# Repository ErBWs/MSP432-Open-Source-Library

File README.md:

# MSP432-Open-Source-Library

欢迎pull request，不过请保持代码风格一致。

> 外设库放在 `/src/bsp` 文件夹内；
> 
> 代码文件命名风格：小写+下划线 `e.g. baudrate_calculate.c`；
> 
> 函数命名风格：首字母全部大写，尽量不用下划线 `e.g. GetPinLevel()`；
> 
> 函数命名下划线适用情况：同名函数但是属于不同的外设库，比如不同屏幕的显示函数，
> 
> 或者如官方库那样以函数作用来命名，名称很长且要表明是哪个库的函数（请尽量避免这种情况），
> 
> `e.g. TFT180_DisplayUint(), IPS200_DisplayUint()`，
> 
> `GPIO_SetAsInputPinWithPullDownResistor()`；
> 
> 变量名命名风格: 第一个首字母小写，后面都大写 `e.g. baudRate`；

如果代码风格不一致的pull request不一定会被退回但是会被我修改代码风格

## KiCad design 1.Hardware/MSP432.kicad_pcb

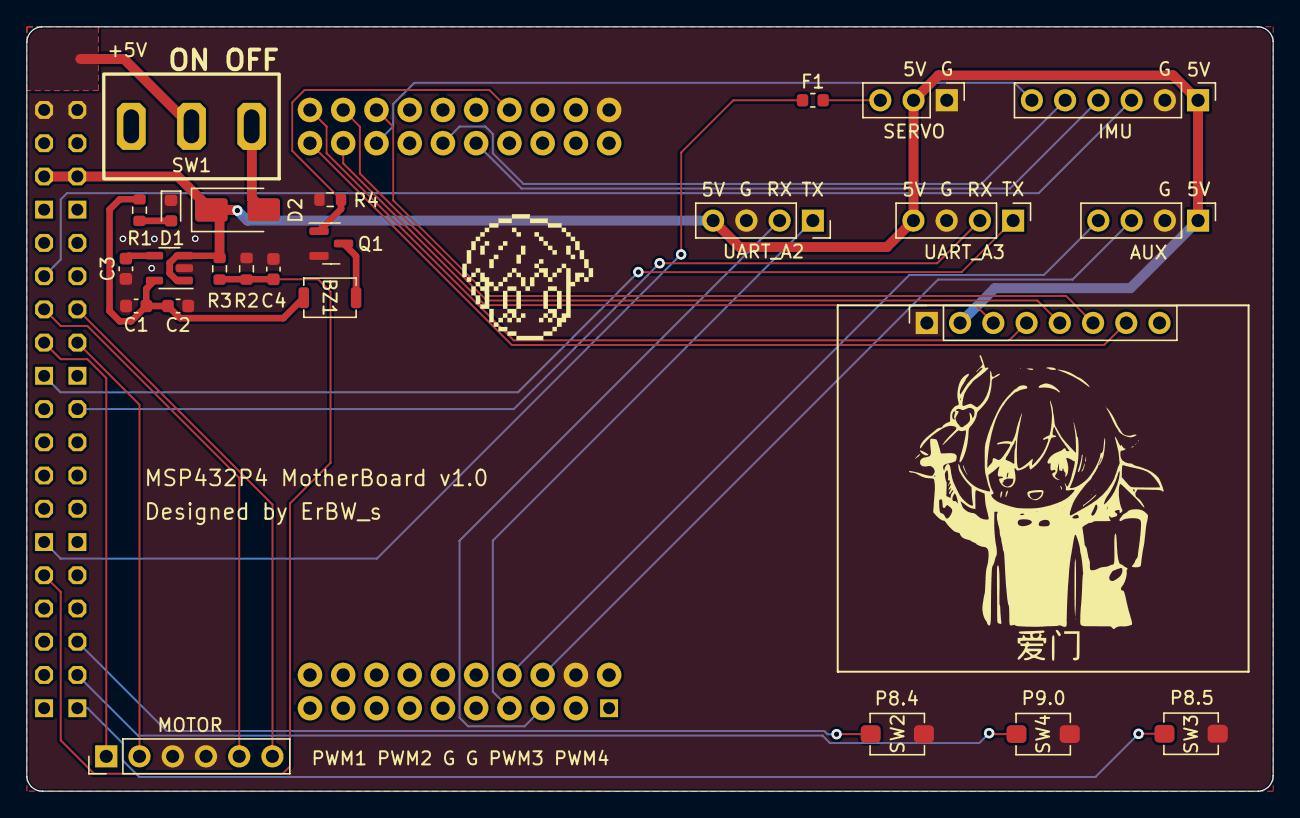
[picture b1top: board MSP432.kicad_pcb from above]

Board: 2 copper layers, 95.2 x 58.4 mm, 26 parts (1 on the bottom side), 33 nets.

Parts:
BZ1: Buzzer; DET-402-G-1
C1: 100nF; C_0603_1608Metric
C2, C4: 10uF; C_0603_1608Metric
C3: 10nF; C_0603_1608Metric
D1: LED; LED_0603_1608Metric
D2: 1N4148W; D_SMA
F1: 500mA; Fuse_0603_1608Metric
J1: SERVO; PinHeader_1x03_P2.54mm_Vertical
J2, J6: Conn_01x06; PinHeader_1x06_P2.54mm_Vertical
J3, J7: Conn_01x04; PinHeader_1x04_P2.54mm_Vertical
J4: Conn_01x08; PinSocket_1x08_P2.54mm_Vertical
J5: Conn_01x04; PinSocket_1x04_P2.54mm_Vertical
Q1: S8050; SOT-23
R1: 5K1; R_0603_1608Metric
R2: 10K; R_0603_1608Metric
R3: 1K; R_0603_1608Metric
R?: 5K1; R_0603_1608Metric
SW1: SW_SPDT; SPDT_MTS_102
SW2, SW3, SW4: 3x4; BUTTON_3x4
U1: RT9013-33GB; SOT-23-5
U2: MSP-EXP432P401R

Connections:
+3V3: BZ1.1 (-), C1.1, C2.1, R1.1, U1.5 (VOUT)
+5V: D2.1 (K), J1.2, J3.4, J4.2, J5.4, J6.1, J7.1, R2.1, U1.1 (VIN), U1.3 (EN), U2.73 (5V), U2.74 (5V)
/A2_RX: J5.2, U2.3 (P3.2/PM_UCA2RXD/PM_UCA2SOMI)
/A2_TX: J5.1, U2.4 (P3.3/PM_UCA2TXD/PM_UCA2SIMO)
/A3_RX: J3.2, U2.60 (P9.6/UCA3RXD/UCA3SOMI)
/A3_TX: J3.1, U2.61 (P9.7/UCA3TXD/UCA3SIMO)
/AUX_SCL: J7.3, U2.23 (P6.1/A14)
/AUX_SDA: J7.4, U2.24 (P4.0/A13)
/BATTERY: C4.2, R2.2, R3.1, U2.49 (P5.3/A2)
/BUZZER: Q1.1 (B), R?.1, U2.17 (P5.7/TA2.2/VREF-/VEREF-/C1.6)
/DIR1: J2.2, U2.64 (P7.4/PM_TA1.4/C0.5)
/DIR2: J2.6, U2.66 (P7.6/PM_TA1.2/C0.3)
/ENCODER_A: SW2.1, U2.46 (P8.4/A21)
/ENCODER_B: SW3.1, U2.42 (P8.5/A20)
/IMU_CS: J6.6, U2.33 (P5.1/A4)
/IMU_SDI: J6.4, U2.36 (P6.6/TA2.3/UCB3SIMO/UCB3SDA/C1.1)
/IMU_SDO: J6.5, U2.35 (P6.7/TA2.4/UCB3SOMI/UCB3SCL/C1.0)
/IMU_SPC: J6.3, U2.67 (P10.1/UCB3CLK)
/IPS_CS: J4.7, U2.31 (P3.7/PM_UCB2SOMI/PM_UCB2SCL)
/IPS_DC: J4.6, U2.13 (P5.0/A5)
/IPS_RES: J4.5, U2.12 (P5.2/A3)
/IPS_SCL: J4.3, U2.32 (P3.5/PM_UCB2CLK)
/IPS_SDA: J4.4, U2.11 (P3.6/PM_UCB2SIMO/PM_UCB2SDA)
/KEY_CENTER: SW4.1, U2.44 (P9.0/A17)
/PWM1: J2.1, U2.63 (P7.5/PM_TA1.3/C0.4)
/PWM2: J2.5, U2.65 (P7.7/PM_TA1.1/C0.2)
/SERVO: F1.1, U2.51 (P9.3/TA3.4)
GND: C1.2, C2.2, C3.2, C4.1, D1.1 (K), J1.1, J2.3, J2.4, J3.3, J4.1, J5.3, J6.2, J7.2, Q1.2 (E), R3.2, R?.2, SW2.2, SW3.2, SW4.2, U1.2 (GND), U2.20 (GND), U2.22 (GND), U2.77 (GND), U2.78 (GND)
unnamed: BZ1.2 (+), Q1.3 (C)
unnamed: D1.2 (A), R1.2
unnamed: D2.2 (A), SW1.1 (A)
unnamed: F1.2, J1.3
unnamed: C3.1, U1.4 (NC)

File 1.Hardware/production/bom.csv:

Designator,Footprint,Quantity,Value,LCSC Part #
BZ1,DET-402-G-1,1,Buzzer,
C1,0603,1,100nF,
C2,0603,1,10uF,
C3,0603,1,10nF,
C4,0603,1,10uF,
D1,0603,1,LED,
D2,D_SMA,1,1N4148W,
F1,0603,1,500mA,
J1,PinHeader_1x03_P2.54mm_Vertical,1,SERVO,
"J2, J6",PinHeader_1x06_P2.54mm_Vertical,2,Conn_01x06,
"J3, J7",PinHeader_1x04_P2.54mm_Vertical,2,Conn_01x04,
J4,PinSocket_1x08_P2.54mm_Vertical,1,Conn_01x08,
J5,PinSocket_1x04_P2.54mm_Vertical,1,Conn_01x04,
Q1,SOT-23,1,S8050,
R1,0603,1,5K1,
R2,0603,1,10K,
R3,0603,1,1K,
R4,0603,1,10K,
SW1,SPDT_MTS_102,1,SW_SPDT,
"SW2, SW3, SW4",BUTTON_3x4,3,3x4,
U1,SOT-23-5,1,RT9013-33GB,
U2,MSP-EXP432P401R,1,MSP-EXP432P401R,

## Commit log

2022-10-10 Initial commits
2022-10-10 Create .name
    Initial commit
2022-10-10 Some changes
2022-10-10 config uart interrupt
2022-10-10 Add README
2022-10-11 config isr_uart interrupt function
2022-10-11 Modify code style
2022-10-11 Add some comments
2022-10-11 Fix bug in baudrate_calculate.c
2022-10-11 Clear useless code in isr.c
2022-10-11 Minor changes
2022-10-11 Change comments of PwmInit
2022-10-11 Fix bug of TimerA interrupt init which cause chip to sleep while exiting the interrupt
2022-10-11 二次封装官方中断优先级配置函数
2022-10-11 add shanwai function and uart_putnchar function and config c.json
2022-10-11 add shanwai function to user_comm
2022-10-12 Adjust README.md
2022-10-12 Add files
2022-10-12 add IIC and icm20602
2022-10-12 Add spi and adjust pwm
2022-10-26 Change folder name
2022-10-26 Update gitignore
2022-10-26 Fix bug that .gitignore is not working
2022-10-31 修改版权声明
2022-10-31 初步实现断言功能
2022-11-01 Add some asserts
2022-11-01 Add user folder
2022-11-14 重构项目文件结构，增加Hardware文件夹
2022-11-14 Change .gitignore location
2022-11-14 Fix bug of .gitignore
2022-11-24 Change comments in pwm.h
2022-12-15 系统环境改变，重构文件结构
2023-03-06 Add vofa library
2023-05-21 Add SendData and change file structure
2023-05-22 Now support printf
2023-05-29 初步完成spi和soft_iic库
2023-05-31 Add more spi data process function(without test)
2023-06-01 more imus and fix bug of spi r/w register function
2023-06-10 Change printf init
2023-07-30 grand upgrade of both firmware and hardware
2023-08-11 v1.0 release
